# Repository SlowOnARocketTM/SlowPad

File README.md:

# SlowPad
My Sumbmition to the HackClub Blueprint!
## My Goal
When I started making the SlowPad, I had a goal in mind. I wanted a macro pad that could be versatile. I wanted to be able to switch the macro depending on what I was doing and while it may seem like an easy thing to make, 
I never made anything using **Fusion** and **KiCad**. Since this is my first time using hardware and software together i'm actually quite happy of the result!
### Note
I managed to make all of the 6 switches work however since i messed up my pcb theres no way to make the oled display work.
### Overall Result

### Schematic

### PCB

### Case

## BOM : 
-	1x Seeed XIAO RP2040
-	4x M3x16mm screws
-	6x Blank DSA Keycaps (5Black 1Red)
-	1x 0.91 inch OLED displays (ssd1036)
-	6x MX-Style Switches
-	3D print (2 parts in black)

### Build Image

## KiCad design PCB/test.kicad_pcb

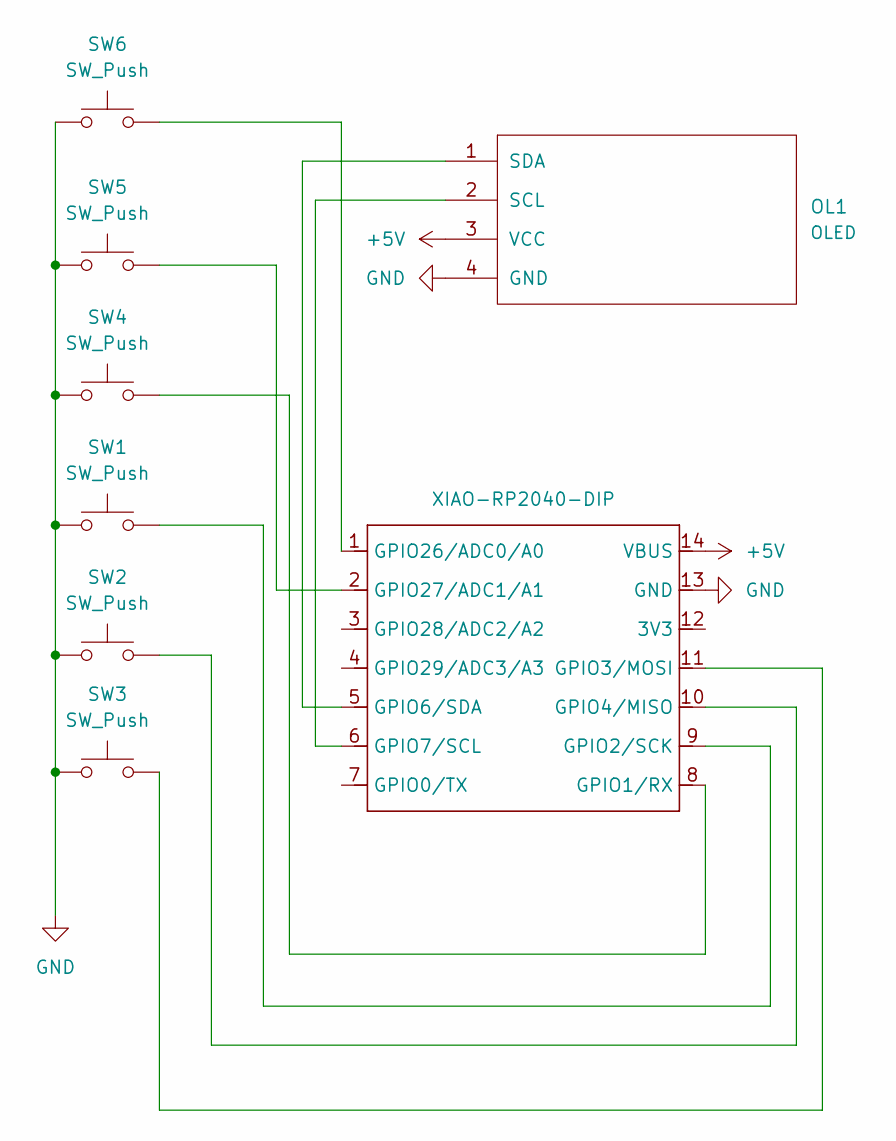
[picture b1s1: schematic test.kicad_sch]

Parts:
OL1: OLED; SSD1306-0.91-OLED-4pin-128x32
SW1, SW2, SW3, SW4, SW5, SW6: SW_Push; SW_Cherry_MX_1.00u_PCB
U1: XIAO-RP2040-DIP

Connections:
+5V: OL1.3 (VCC), U1.14 (VBUS)
GND: OL1.4 (GND), SW1.1, SW2.1, SW3.1, SW4.1, SW5.1, SW6.1, U1.13 (GND)
unnamed: OL1.2 (SCL), U1.6 (GPIO7/SCL)
unnamed: OL1.1 (SDA), U1.5 (GPIO6/SDA)
unnamed: SW4.2, U1.8 (GPIO1/RX)
unnamed: SW1.2, U1.9 (GPIO2/SCK)
unnamed: SW3.2, U1.11 (GPIO3/MOSI)
unnamed: SW2.2, U1.10 (GPIO4/MISO)
unnamed: SW6.2, U1.1 (GPIO26/ADC0/A0)
unnamed: SW5.2, U1.2 (GPIO27/ADC1/A1)

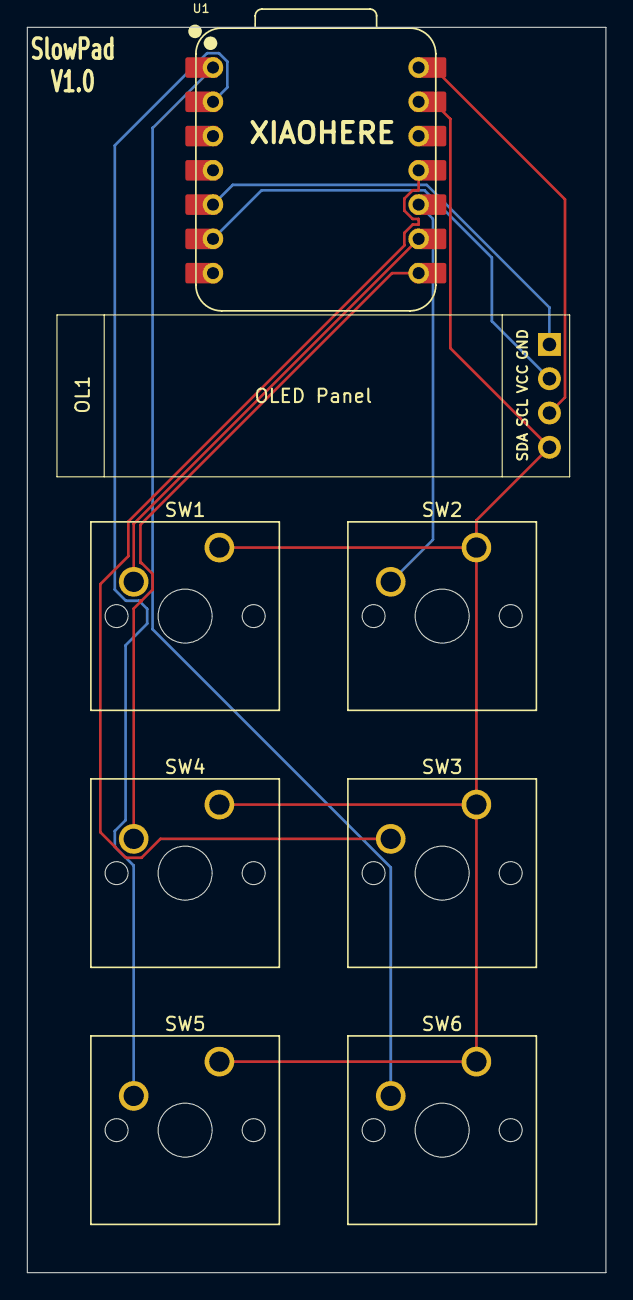
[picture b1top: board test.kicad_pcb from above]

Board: 2 copper layers, 42.9 x 92.3 mm, 8 parts (0 on the bottom side), 10 nets.

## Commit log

2025-11-29 INIT
2025-11-29 Update BOM with keycap colors and 3D print details
    Specify the colors of the keycaps and clarify 3D print parts.
2025-12-31 Update README with OLED display note and final image
    Added a note about the OLED display issue and included a final result image.
2025-12-31 Rename section from 'Final Result' to 'Build Image'
